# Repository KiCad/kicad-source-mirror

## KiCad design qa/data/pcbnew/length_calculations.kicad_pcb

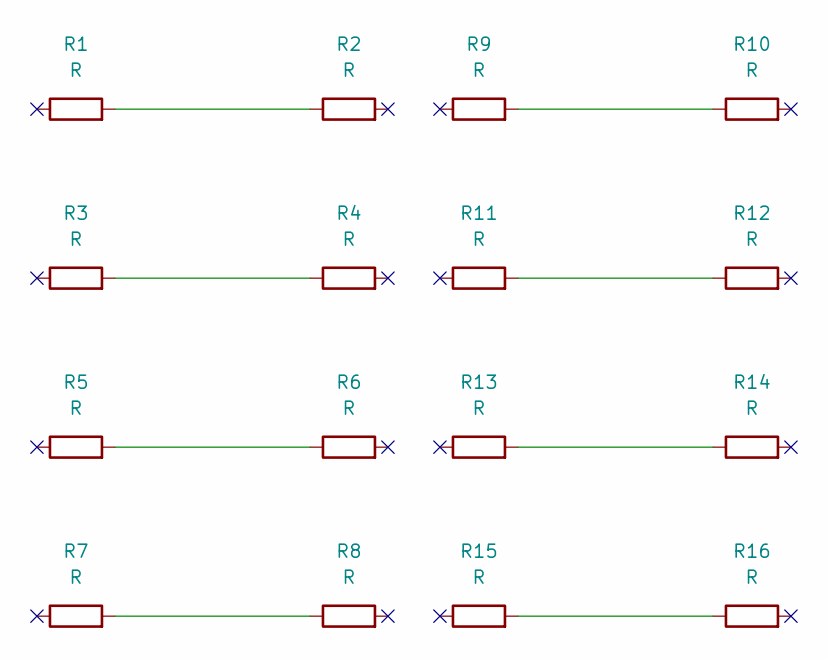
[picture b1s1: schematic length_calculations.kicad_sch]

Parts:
R1, R2, R3, R4, R5, R6, R7, R8, R9, R10, R11, R12, R13, R14, R15, R16: R; R_0805_2012Metric

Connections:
unnamed: R1.2, R2.1
unnamed: R3.2, R4.1
unnamed: R5.2, R6.1
unnamed: R7.2, R8.1
unnamed: R9.2, R10.1
unnamed: R11.2, R12.1
unnamed: R13.2, R14.1
unnamed: R15.2, R16.1

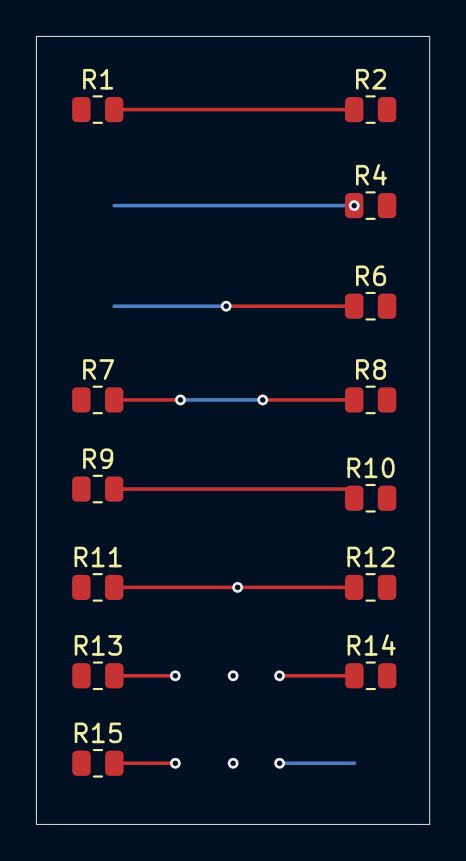
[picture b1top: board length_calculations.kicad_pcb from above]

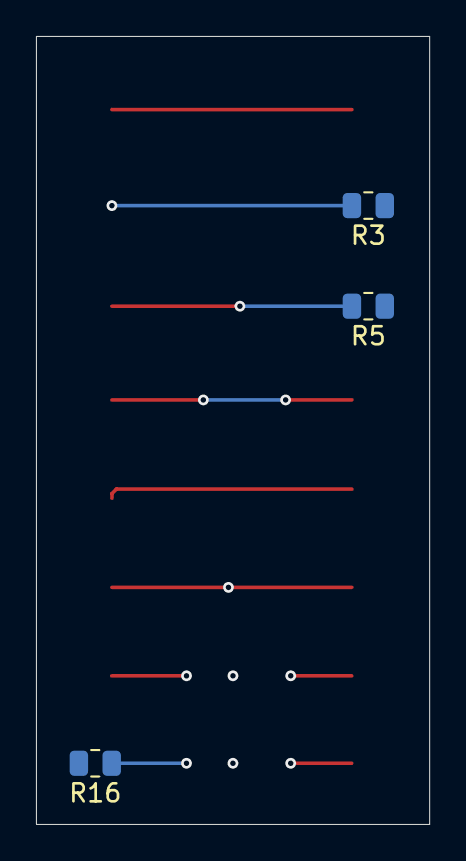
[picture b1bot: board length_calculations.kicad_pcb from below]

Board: 4 copper layers, 21.8 x 43.8 mm, 16 parts (3 on the bottom side), 8 nets.

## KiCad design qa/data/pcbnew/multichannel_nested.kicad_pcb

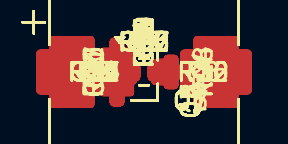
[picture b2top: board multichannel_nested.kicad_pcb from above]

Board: 2 copper layers, 64 parts (0 on the bottom side), 32 nets.

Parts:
C1, C2, C4, C5, C7, C8, C10, C11, C13, C14, C16, C17, C19, C20, C22, C23: C; C_0805_2012Metric
C3, C6, C9, C12, C15, C18, C21, C24: C_Polarized; CP_Elec_10x10
Q1, Q2, Q3, Q4, Q5, Q6, Q7, Q8: BC547; SOT-23_Handsoldering
R1, R2, R3, R4, R5, R6, R7, R8, R9, R10, R11, R12, R13, R14, R15, R16, R17, R18, R19, R20, R21, R22, R23, R24, R25, R26, R27, R28, R29, R30, R31, R32: R; R_0805_2012Metric

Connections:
/FirstChannel/A: C2.1, C4.2
/FirstChannel/B: C5.1, C7.2
/FirstChannel/C: C8.1, C10.2
/SecondChannel/A: C13.2, C17.1
/SecondChannel/B: C14.1, C22.2
/SecondChannel/C: C19.2, C23.1
GND: C3.2, C6.2, C9.2, C12.2, C15.2, C18.2, C21.2, C24.2, R2.2, R4.2, R6.2, R8.2, R10.2, R12.2, R14.2, R16.2, R18.2, R20.2, R22.2, R24.2, R26.2, R28.2, R30.2, R32.2
unnamed: C1.1, Q1.2 (B), R1.2, R2.1
unnamed: C2.2, Q1.1 (C), R3.2
unnamed: C3.1, Q1.3 (E), R4.1
unnamed: C4.1, Q2.2 (B), R5.2, R6.1
unnamed: C5.2, Q2.1 (C), R7.2
unnamed: C6.1, Q2.3 (E), R8.1
unnamed: C7.1, Q3.2 (B), R9.2, R10.1
unnamed: C8.2, Q3.1 (C), R11.2
unnamed: C9.1, Q3.3 (E), R12.1
unnamed: C10.1, Q4.2 (B), R13.2, R14.1
unnamed: C11.2, Q4.1 (C), R15.2
unnamed: C12.1, Q4.3 (E), R16.1
unnamed: C13.1, Q5.2 (B), R17.2, R18.1
unnamed: C14.2, Q5.1 (C), R19.2
unnamed: C15.1, Q5.3 (E), R20.1
unnamed: C16.1, Q6.2 (B), R21.2, R22.1
unnamed: C17.2, Q6.1 (C), R23.2
unnamed: C18.1, Q6.3 (E), R24.1
unnamed: C19.1, Q7.2 (B), R25.2, R26.1
unnamed: C20.2, Q7.1 (C), R27.2
unnamed: C21.1, Q7.3 (E), R28.1
unnamed: C22.1, Q8.2 (B), R29.2, R30.1
unnamed: C23.2, Q8.1 (C), R31.2
unnamed: C24.1, Q8.3 (E), R32.1
VCC: R1.1, R3.1, R5.1, R7.1, R9.1, R11.1, R13.1, R15.1, R17.1, R19.1, R21.1, R23.1, R25.1, R27.1, R29.1, R31.1
